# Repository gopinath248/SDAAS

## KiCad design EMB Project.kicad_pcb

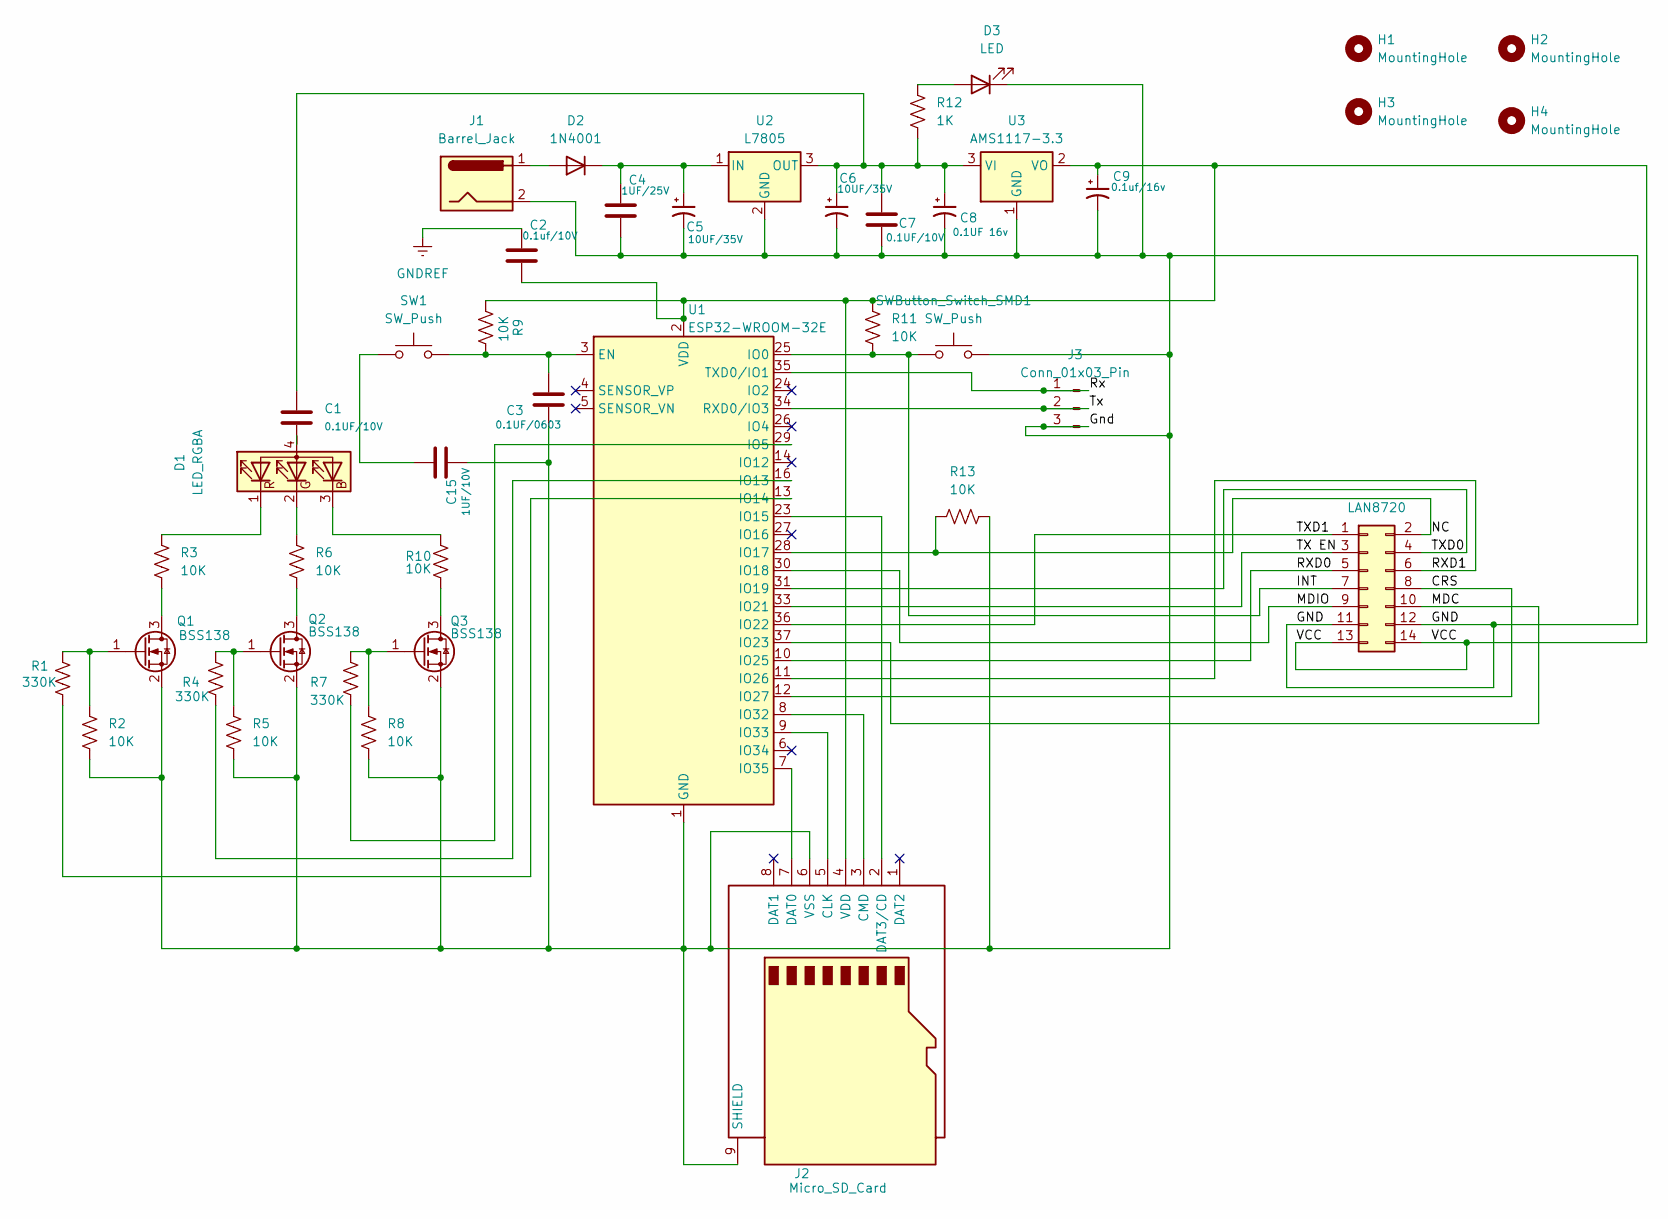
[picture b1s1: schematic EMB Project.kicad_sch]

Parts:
C1, C7: 0.1UF/10V; C_0603_1608Metric
C2: 0.1uf/10V; C_0603_1608Metric
C3: 0.1UF/0603; C_0603_1608Metric
C4: 1UF/25V; C_0603_1608Metric
C5, C6: 10UF/35V; C_0805_2012Metric
C8: 0.1UF 16v; C_0805_2012Metric
C9: 0.1uf/16v; C_0805_2012Metric
C15: 1UF/10V; C_0603_1608Metric
D1: LED_RGBA; LED_D5.0mm-4_RGB
D2: 1N4001; D_SMA
D3: LED; LED_D3.0mm
H1, H2, H3, H4: MountingHole; MountingHole_2.7mm_M2.5
J1: Barrel_Jack; BarrelJack_CUI_PJ-102AH_Horizontal
J2: Micro_SD_Card; microSD_HC_Hirose_DM3AT-SF-PEJM5
J3: Conn_01x03_Pin; PinHeader_1x03_P2.54mm_Vertical
J4: LAN8720; PinHeader_2x07_P2.54mm_Vertical
Q1, Q2, Q3: BSS138; SOT-23
R1, R4, R7: 330K; R_0805_2012Metric
R2, R3, R5, R6, R8, R9, R10, R11, R13: 10K; R_0805_2012Metric
R12: 1K; R_0805_2012Metric
SW1: SW_Push; SW_PUSH_6mm
SWButton_Switch_SMD1: SW_Push; SW_Tactile_SPST_NO_Straight_CK_PTS636Sx25SMTRLFS
U1: ESP32-WROOM-32E; ESP32-WROOM-32
U2: L7805; TO-220-3_Vertical
U3: AMS1117-3.3; SOT-223-3_TabPin2

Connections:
/CRS: J4.8, U1.12 (IO27)
/GND: C3.2, C4.2, C5.2, C6.2, C7.2, C8.2, C9.2, C15.2, D3.1 (K), J1.2, J2.6 (VSS), J2.9 (SHIELD), J3.3, J4.11, J4.12, Q1.2 (S), Q2.2 (S), Q3.2 (S), R2.2, R5.2, R8.2, R13.1, SWButton_Switch_SMD1.2, U1.1 (GND), U1.15 (GND), U1.38 (GND), U1.39 (GND), U2.2 (GND), U3.1 (GND)
/INT: J4.7, R11.2, SWButton_Switch_SMD1.1, U1.25 (IO0)
/MDC: J4.10, U1.37 (IO23)
/MDIO: J4.9, U1.30 (IO18)
/NC: J4.2, R13.2, U1.28 (IO17)
/RXD0: J4.5, U1.10 (IO25)
/RXD1: J4.6, U1.11 (IO26)
/Rx: J3.1, U1.35 (TXD0/IO1)
/TX EN: J4.3, U1.33 (IO21)
/TXD0: J4.4, U1.31 (IO19)
/TXD1: J4.1, U1.36 (IO22)
/Tx: J3.2, U1.34 (RXD0/IO3)
/VCC: C2.2, C9.1, J2.4 (VDD), J4.13, J4.14, R9.2, R11.1, U1.2 (VDD), U3.2 (VO)
GNDREF: C2.1
unnamed: C15.1, SW1.1
unnamed: C1.2, D1.4 (A)
unnamed: D1.3 (BK), R10.1
unnamed: D1.2 (GK), R6.1
unnamed: D1.1 (RK), R3.1
unnamed: D2.2 (A), J1.1
unnamed: C4.1, C5.1, D2.1 (K), U2.1 (IN)
unnamed: D3.2 (A), R12.1
unnamed: J2.5 (CLK), U1.9 (IO33)
unnamed: J2.3 (CMD), U1.8 (IO32)
unnamed: J2.7 (DAT0), U1.7 (IO35)
unnamed: J2.2 (DAT3/CD), U1.23 (IO15)
unnamed: Q1.3 (D), R3.2
unnamed: Q1.1 (G), R1.1, R2.1
unnamed: Q2.3 (D), R6.2
unnamed: Q2.1 (G), R4.1, R5.1
unnamed: Q3.3 (D), R10.2
unnamed: Q3.1 (G), R7.1, R8.1
unnamed: C3.1, R9.1, SW1.2, U1.3 (EN)
unnamed: R7.2, U1.29 (IO5)
unnamed: R4.2, U1.16 (IO13)
unnamed: R1.2, U1.13 (IO14)
unnamed: C1.1, C6.1, C7.1, C8.1, R12.2, U2.3 (OUT), U3.3 (VI)

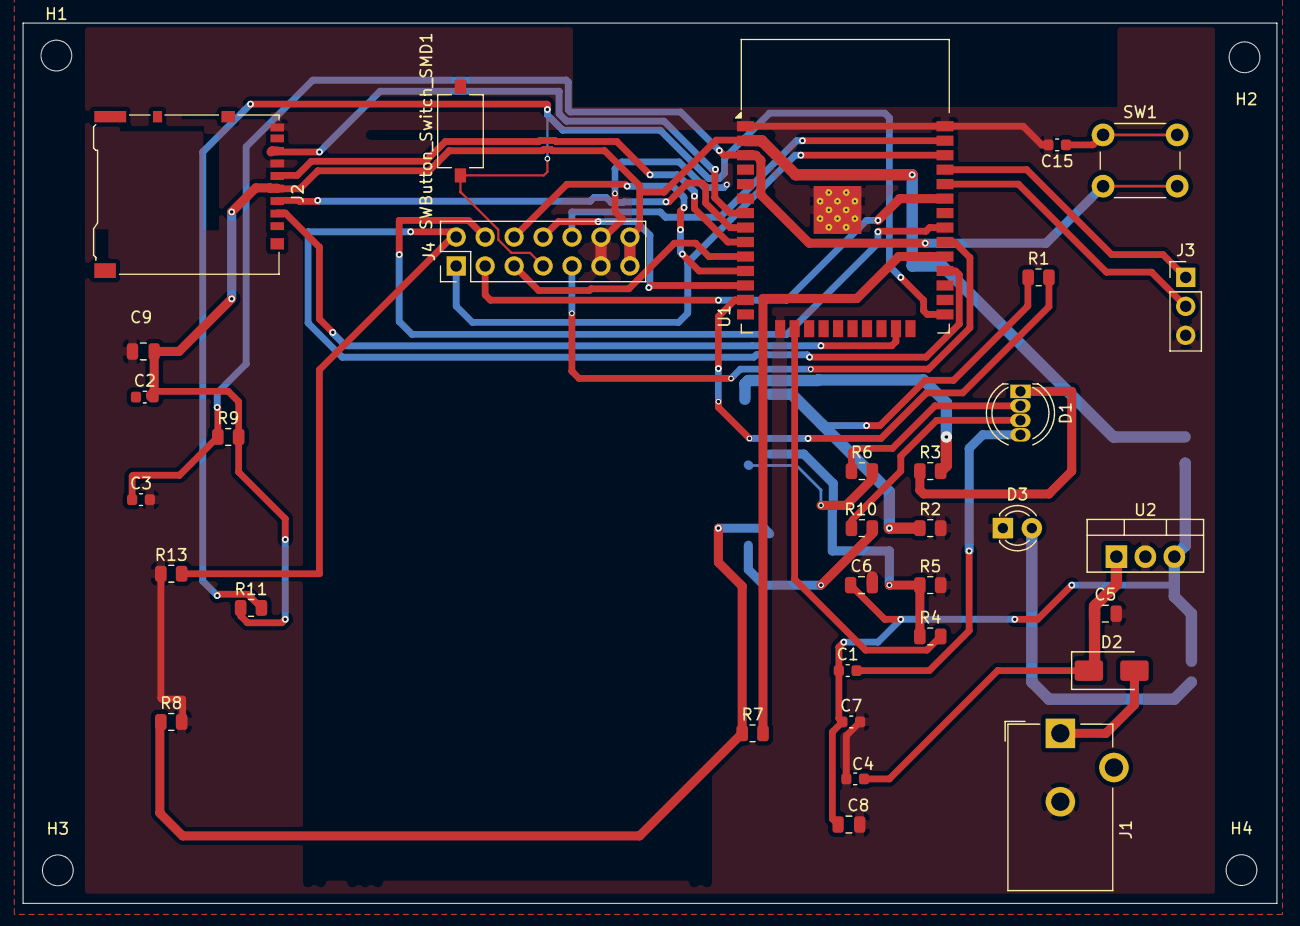
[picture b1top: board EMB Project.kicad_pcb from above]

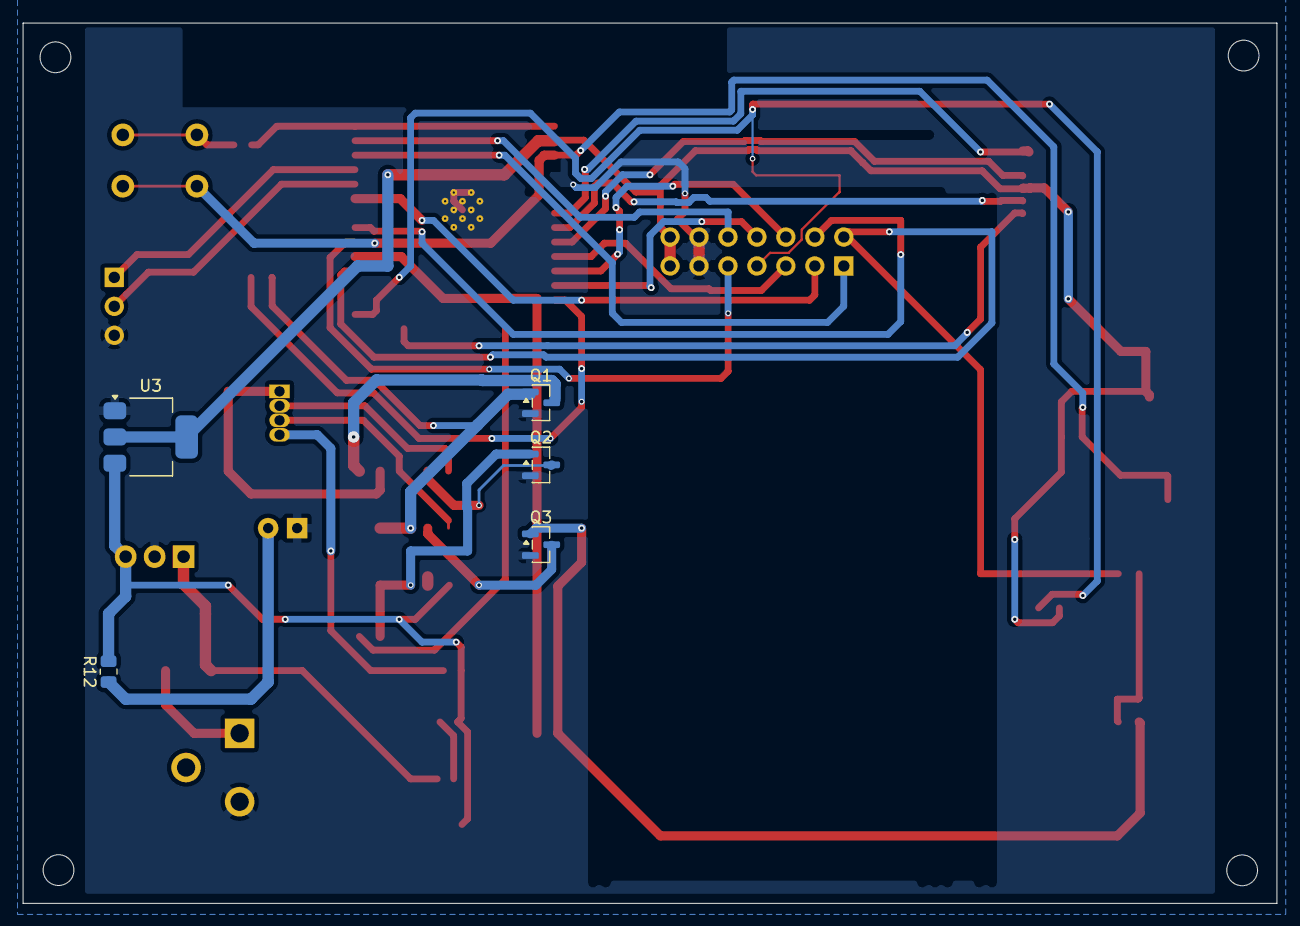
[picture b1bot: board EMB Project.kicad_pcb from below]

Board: 2 copper layers, 110.0 x 77.2 mm, 42 parts (5 on the bottom side), 37 nets.
